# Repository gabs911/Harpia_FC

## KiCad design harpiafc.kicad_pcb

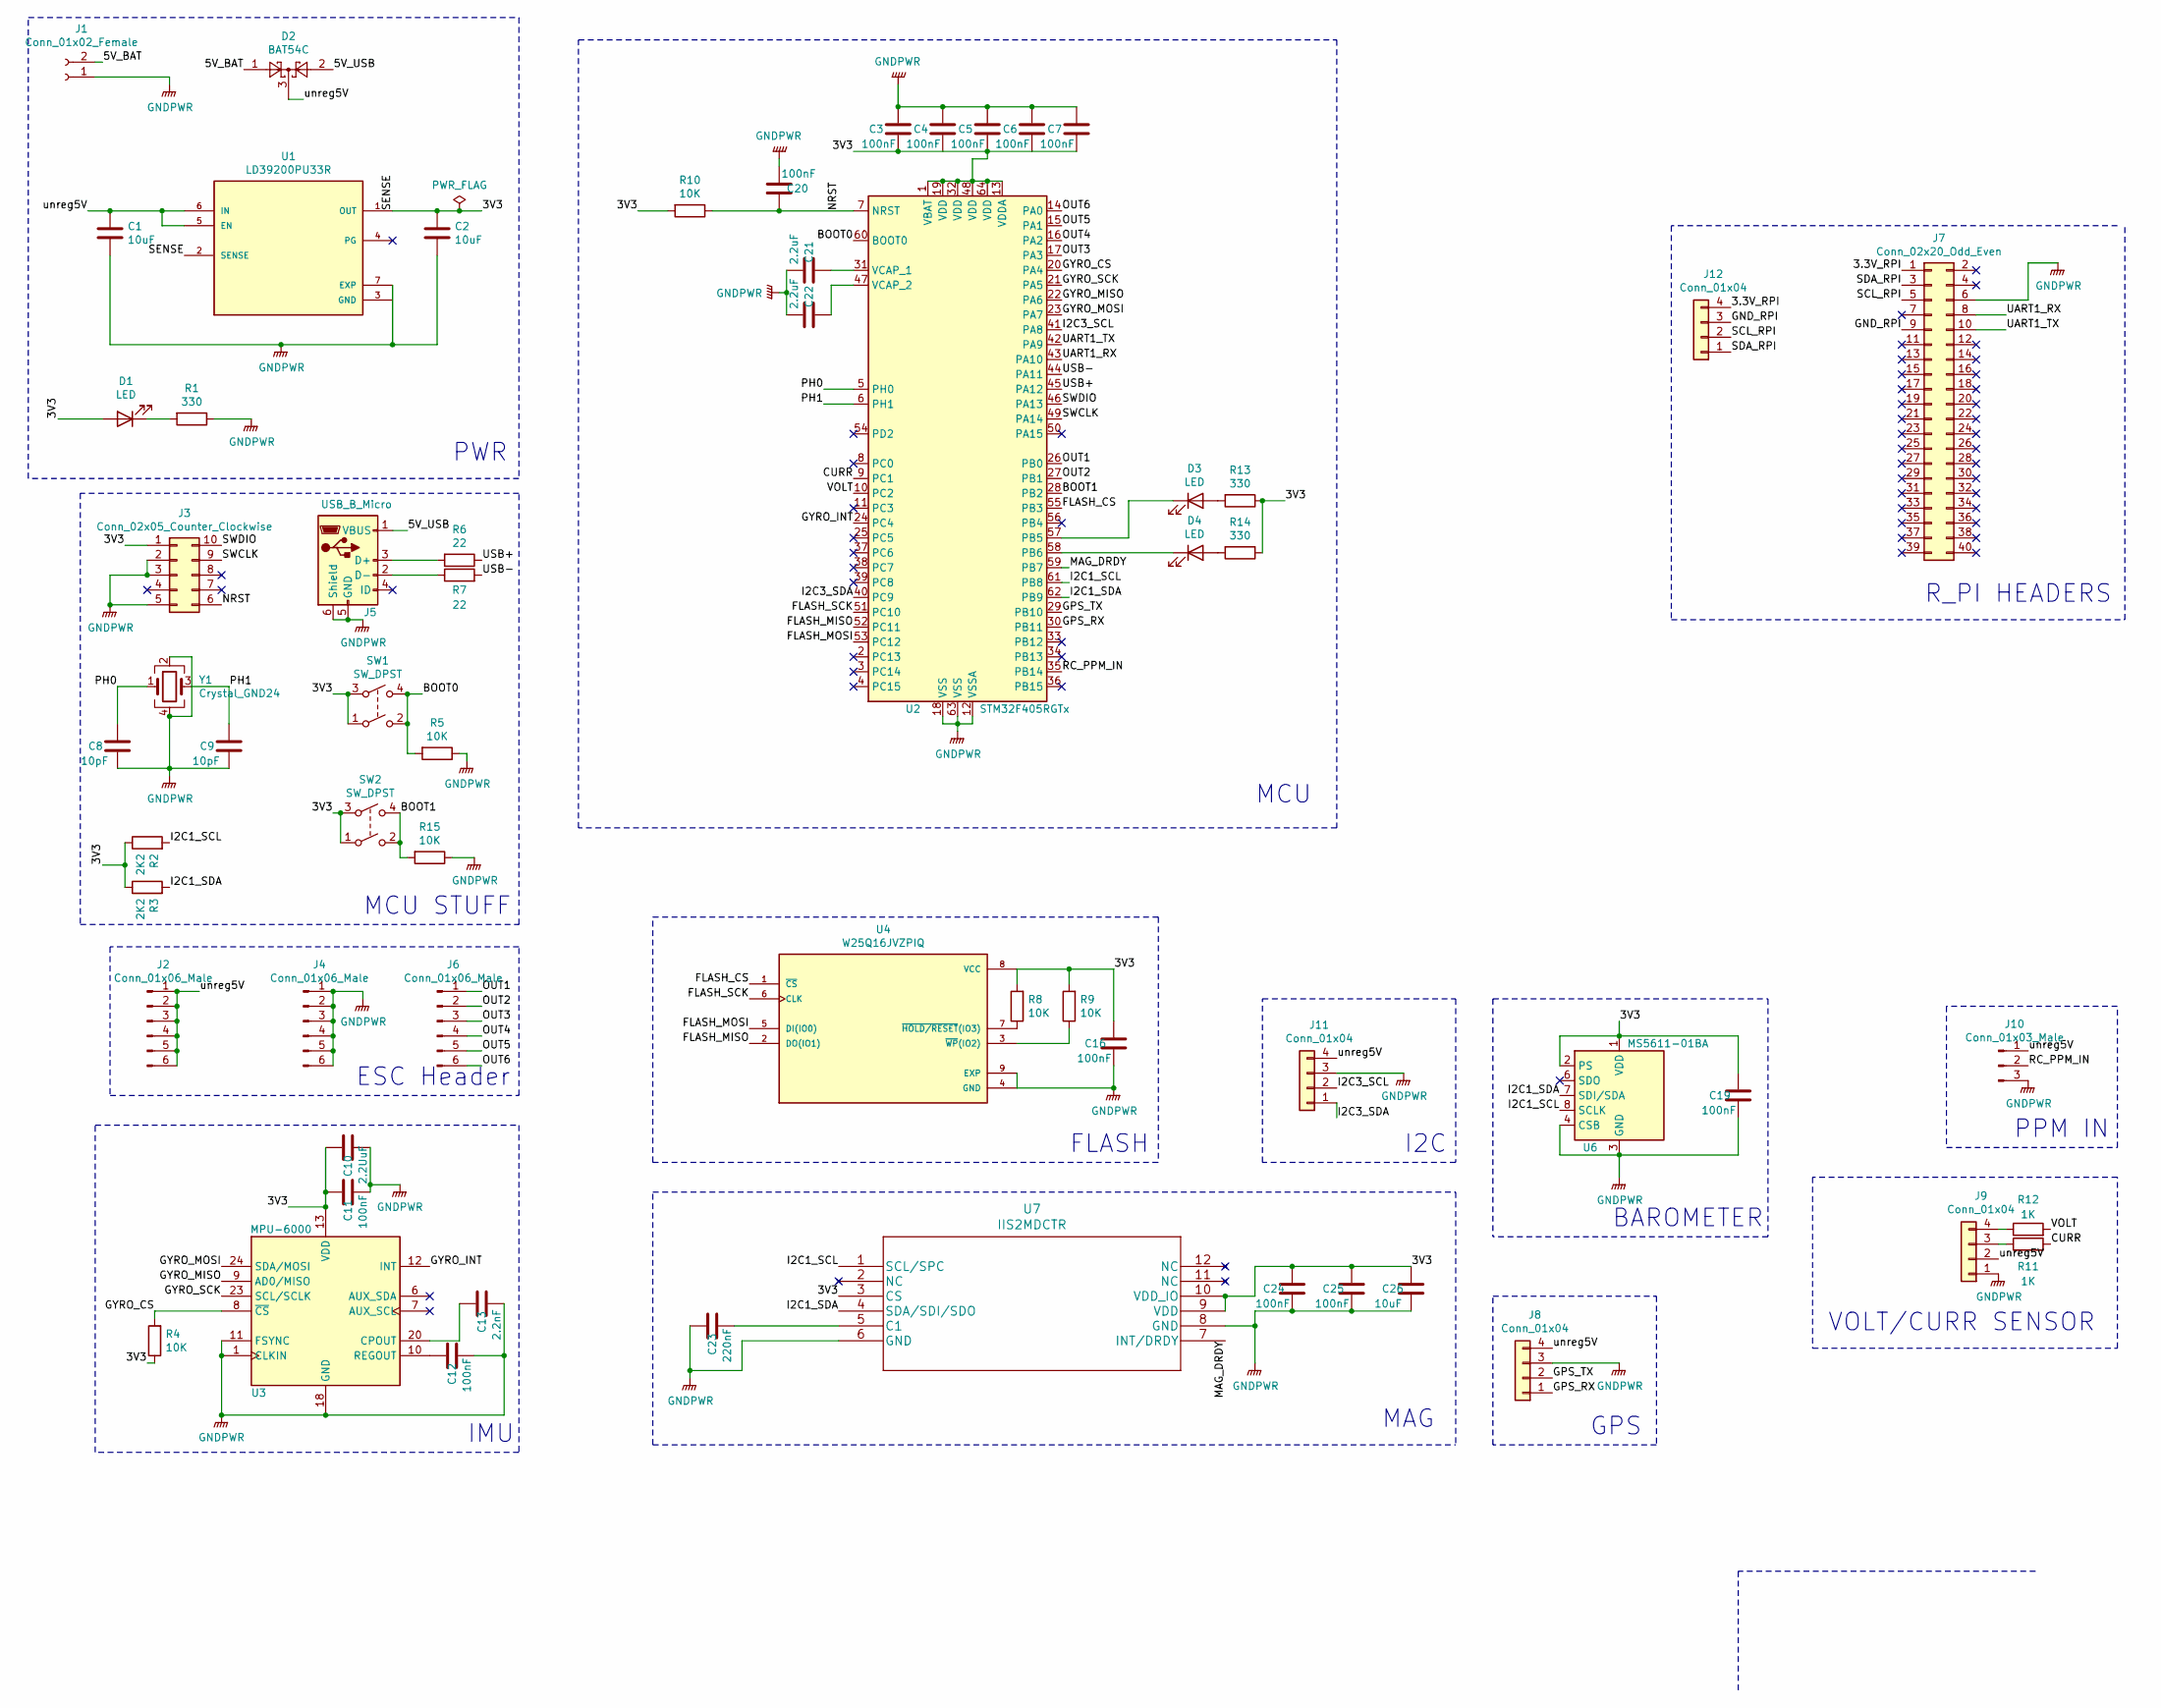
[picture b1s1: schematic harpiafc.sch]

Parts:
C1, C2, C26: 10uF; C_0805_2012Metric
C3, C4, C5, C6, C7, C11, C12, C16, C19, C20, C24, C25: 100nF; C_0805_2012Metric
C8, C9: 10pF; C_0805_2012Metric
C10: 2.2UuF; C_0805_2012Metric
C13: 2.2nF; C_0805_2012Metric
C21, C22: 2.2uF; C_0805_2012Metric
C23: 220nF; C_0805_2012Metric
D1, D3, D4: LED; LED_0805_2012Metric
D2: BAT54C; SOT-23
J1: Conn_01x02_Female; JST_EH_S2B-EH_1x02_P2.50mm_Horizontal
J2, J4, J6: Conn_01x06_Male; PinHeader_1x06_P2.54mm_Vertical
J3: Conn_02x05_Counter_Clockwise; PinHeader_2x05_P2.54mm_Vertical
J5: USB_B_Micro; USB_Micro-B_Molex_47346-0001
J7: Conn_02x20_Odd_Even; PinSocket_2x20_P2.54mm_Vertical
J8: Conn_01x04; JST_EH_B4B-EH-A_1x04_P2.50mm_Vertical
J9, J11, J12: Conn_01x04; JST_EH_S4B-EH_1x04_P2.50mm_Horizontal
J10: Conn_01x03_Male; PinHeader_1x03_P2.54mm_Vertical
R1, R13, R14: 330; R_0603_1608Metric
R2, R3: 2K2; R_0603_1608Metric
R4, R5, R8, R9, R10, R15: 10K; R_0603_1608Metric
R6, R7: 22; R_0603_1608Metric
R11, R12: 1K; R_0603_1608Metric
SW1, SW2: SW_DPST; SW_SPST_EVQP0
U1: LD39200PU33R; SON95P300X300X100-7N; PARTREV 3
U2: STM32F405RGTx; LQFP-64_10x10mm_P0.5mm
U3: MPU-6000; InvenSense_QFN-24_4x4mm_P0.5mm
U4: W25Q16JVZPIQ; SON127P500X600X80-9N
U6: MS5611-01BA; LGA-8_3x5mm_P1.25mm
U7: IIS2MDCTR
Y1: Crystal_GND24; Crystal_SMD_Abracon_ABM8G-4Pin_3.2x2.5mm

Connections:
/3.3V_RPI: J7.1, J12.4
/3V3: C2.1, C3.2, C5.2, C7.2, C10.1, C11.1, C16.1, C19.1, C24.1, C25.1, C26.1, D1.2 (A), J3.1, R2.1, R3.1, R4.1, R8.2, R9.2, R10.2, R13.1, R14.1, SW1.1, SW1.3, SW2.1, SW2.3, U1.1 (OUT), U1.2 (SENSE), U2.1 (VBAT), U2.13 (VDDA), U2.19 (VDD), U2.32 (VDD), U2.48 (VDD), U2.64 (VDD), U3.13 (VDD), U4.8 (VCC), U6.1 (VDD), U6.2 (PS), U7.3 (CS), U7.9 (VDD), U7.10 (VDD_IO)
/5V_BAT: D2.1, J1.2
/5V_USB: D2.2, J5.1 (VBUS)
/BOOT0: R5.2, SW1.2, SW1.4, U2.60 (BOOT0)
/BOOT1: R15.2, SW2.2, SW2.4, U2.28 (PB2)
/CURR: R12.2, U2.9 (PC1)
/FLASH_CS: U2.55 (PB3), U4.1 (~CS)
/FLASH_MISO: U2.52 (PC11), U4.2 (DO(IO1))
/FLASH_MOSI: U2.53 (PC12), U4.5 (DI(IO0))
/FLASH_SCK: U2.51 (PC10), U4.6 (CLK)
/GND_RPI: J7.9, J12.3
/GPS_RX: J8.1, U2.30 (PB11)
/GPS_TX: J8.2, U2.29 (PB10)
/GYRO_CS: R4.2, U2.20 (PA4), U3.8 (~CS)
/GYRO_INT: U2.24 (PC4), U3.12 (INT)
/GYRO_MISO: U2.22 (PA6), U3.9 (AD0/MISO)
/GYRO_MOSI: U2.23 (PA7), U3.24 (SDA/MOSI)
/GYRO_SCK: U2.21 (PA5), U3.23 (SCL/SCLK)
/I2C1_SCL: R2.2, U2.61 (PB8), U6.8 (SCLK), U7.1 (SCL/SPC)
/I2C1_SDA: R3.2, U2.62 (PB9), U6.7 (SDI/SDA), U7.4 (SDA/SDI/SDO)
/I2C3_SCL: J11.2, U2.41 (PA8)
/I2C3_SDA: J11.1, U2.40 (PC9)
/MAG_DRDY: U2.59 (PB7), U7.7 (INT/DRDY)
/NRST: C20.1, J3.6, R10.1, U2.7 (NRST)
/OUT1: J6.1, U2.26 (PB0)
/OUT2: J6.2, U2.27 (PB1)
/OUT3: J6.3, U2.17 (PA3)
/OUT4: J6.4, U2.16 (PA2)
/OUT5: J6.5, U2.15 (PA1)
/OUT6: J6.6, U2.14 (PA0)
/PH0: C8.1, U2.5 (PH0), Y1.1
/PH1: C9.1, U2.6 (PH1), Y1.3
/RC_PPM_IN: J10.2, U2.35 (PB14)
/SCL_RPI: J7.5, J12.2
/SDA_RPI: J7.3, J12.1
/SWCLK: J3.9, U2.49 (PA14)
/SWDIO: J3.10, U2.46 (PA13)
/UART1_RX: J7.8, U2.43 (PA10)
/UART1_TX: J7.10, U2.42 (PA9)
/USB+: R6.1, U2.45 (PA12)
/USB-: R7.2, U2.44 (PA11)
/VOLT: R11.2, U2.10 (PC2)
/unreg5V: C1.1, D2.3, J2.1, J2.2, J2.3, J2.4, J2.5, J2.6, J8.4, J9.2, J10.1, J11.4, U1.5 (EN), U1.6 (IN)
GNDPWR: C1.2, C2.2, C3.1, C4.1, C5.1, C6.1, C7.1, C8.2, C9.2, C10.2, C11.2, C12.2, C13.2, C16.2, C19.2, C20.2, C21.2, C22.2, C23.1, C24.2, C25.2, C26.2, J1.1, J3.2, J3.3, J3.5, J4.1, J4.2, J4.3, J4.4, J4.5, J4.6, J5.5 (GND), J5.6 (Shield), J7.6, J8.3, J9.1, J10.3, J11.3, R1.1, R5.1, R15.1, U1.3 (GND), U1.7 (EXP), U2.12 (VSSA), U2.18 (VSS), U2.63 (VSS), U3.1 (CLKIN), U3.11 (FSYNC), U3.18 (GND), U4.4 (GND), U4.9 (EXP), U6.3 (GND), U6.4 (CSB), U6.5 (CSB), U7.6 (GND), U7.8 (GND), Y1.2, Y1.4
unnamed: C12.1, U3.10 (REGOUT)
unnamed: C13.1, U3.20 (CPOUT)
unnamed: C21.1, U2.31 (VCAP_1)
unnamed: C22.1, U2.47 (VCAP_2)
unnamed: C23.2, U7.5 (C1)
unnamed: D1.1 (K), R1.2
unnamed: D3.1 (K), U2.57 (PB5)
unnamed: D3.2 (A), R13.2
unnamed: D4.1 (K), U2.58 (PB6)
unnamed: D4.2 (A), R14.2
unnamed: J5.2 (D-), R7.1
unnamed: J5.3 (D+), R6.2
unnamed: J9.3, R12.1
unnamed: J9.4, R11.1
unnamed: R8.1, U4.7 (~HOLD/RESET~(IO3))
unnamed: R9.1, U4.3 (~WP~(IO2))

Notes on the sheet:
GPS
PWR
MCU STUFF
ESC Header
IMU
FLASH
MAG
I2C
BAROMETER
MCU
PPM IN
VOLT/CURR SENSOR
R_PI HEADERS

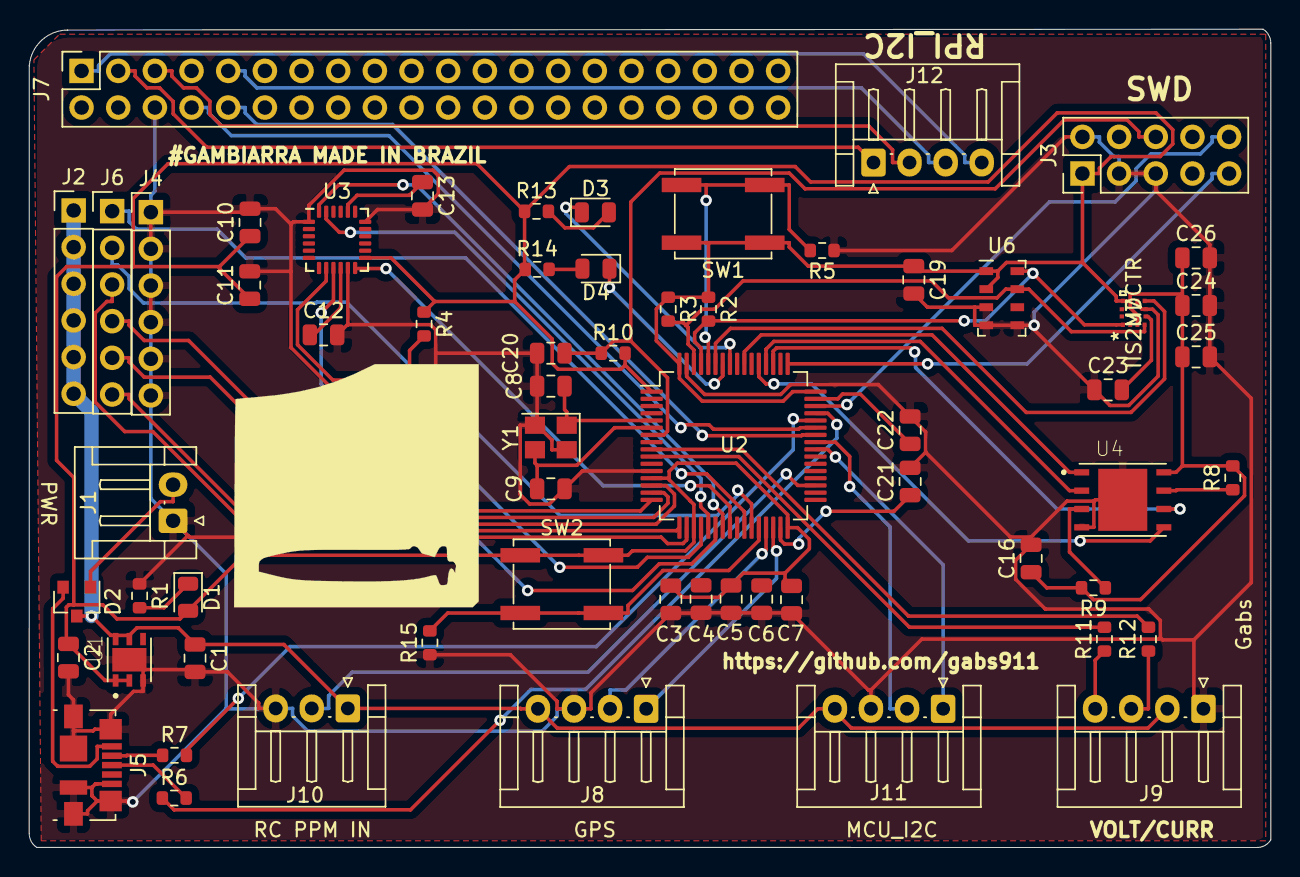
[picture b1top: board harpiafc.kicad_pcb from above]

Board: 2 copper layers, 86.0 x 56.7 mm, 62 parts (0 on the bottom side), 61 nets.

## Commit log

2021-03-13 Added v1.0 files
2021-03-21 PCB modified
2021-03-21 Added pdf schematic

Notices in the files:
parts and their libraries:
Copyright 2016 Accelerated Designs. All rights reserved.
